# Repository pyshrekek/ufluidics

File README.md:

# ufluidics

Firmware for an Elegoo Mega 2560 R3 driving five NEMA17 syringe pumps on a microfluidic device.

Two input pumps push a fixed total flow into the chip at a fixed ratio to each other.
Three output pumps withdraw exactly that same total, split three ways.
Two potentiometers set the output split live, and a maintained switch arms and disarms the system.

Mass balance holds by construction, not by tuning.
No pump is ever commanded directly: one total flow constant drives both inputs (by a fixed ratio) and all three outputs (by fractions that sum to 1.0).
There is one source of truth for flow in the entire program.

## Dependency

**AccelStepper** by Mike McCauley.
Arduino IDE: `Tools > Manage Libraries`, search "AccelStepper", install.

Used in constant-speed mode only.
`runSpeed()` is polled for all five pumps on every loop pass and no acceleration ramp is configured, because steady volumetric flow is the whole point and a ramp would corrupt the mass balance every time a pot moved.

## Repository layout

```
ufluidics/
  README.md          this file - the Mega firmware: wiring, calibration, verification
  HARDWARE.md        PCB spec for the ESP32-S3 revision

  arduino/ufluidics/ Mega 2560 firmware (Arduino IDE)
    ufluidics.ino
    config.h

  firmware/          ESP32-S3 firmware (PlatformIO) - see firmware/README.md
    platformio.ini
    include/config.h
    src/{flow,motion,main}
    data/            LittleFS web assets

  hardware/          KiCad project
    ufluidics.kicad_{pro,sch,pcb}
```

Two builds coexist deliberately: the Mega rig stays working while the ESP32 board is developed. `src/flow.cpp` in the ESP32 build is the AVR flow math ported without modification - see `firmware/README.md`.

**`arduino/ufluidics/` must keep that directory name.** The Arduino IDE requires a sketch folder named exactly after its `.ino`. The repository root can be named anything.

The three KiCad files must also keep a shared basename - that is a KiCad requirement, not a convention. Rename all three together or none.

## Configuration at a glance

At 1/16 microstepping with a 2 mm lead screw and a 14.5 mm syringe bore:

| Quantity | Value |
|---|---|
| steps/mm | 1600 |
| uL/mm | 165.13 |
| steps/uL | 9.69 |
| uL per step | 0.103 |
| Full 10 mL stroke | 60.6 mm, 96 893 steps |

Input flow is **fixed in firmware**, not pot-controlled:

| Pump | Flow | Share of total | Step rate |
|---|---|---|---|
| IN1 | 70 uL/min | 6.25% | 11.3 steps/s |
| IN2 | 1050 uL/min | 93.75% | 169.6 steps/s |
| **Total** | **1120 uL/min (1.12 mL/min)** | - | - |
| OUT3 at a 100% split (worst case) | 1120 uL/min | - | 180.9 steps/s |

The two pots only set how that fixed total is divided between the three outputs.

Flow is smooth: the 0.103 uL step quantum is delivered 11 to 181 times a second, so pulsatility is not a concern.
Peak rate is 181 steps/s against the 2000 steps/s ceiling - an 11x margin, and the shortest step interval is 5.5 ms.
That is comfortably inside where a polled step generator is accurate, so AccelStepper's loop-latency behaviour is not a practical concern at these rates.

### Barrel capacity is the binding constraint - read this

The mechanics are comfortable at these rates; the syringes are what limit a run.
Every barrel is currently 10 mL, and the 15:1 input ratio means they do not last remotely the same time:

| Pump | Flow | 10 mL barrel lasts |
|---|---|---|
| IN1 | 70 uL/min | 143 min |
| IN2 | 1050 uL/min | **9.5 min** |
| OUT3 at a 100% split | 1120 uL/min | **8.9 min** |

**IN2 is the limiting pump.** A 10 mL barrel gives it under a 10 minute run.

For both inputs to exhaust together, barrel volumes want the same 15:1 proportion as the flows - 10 mL on IN1 against 150 mL on IN2 would both run 143 minutes. A 60 mL syringe on IN2 gives 57 minutes, which is usually the practical sweet spot.
Nothing in firmware can extend this; it is a straight volume-over-rate limit.

The output side needs the same thought.
The three outputs collectively receive the full 1120 uL/min, so whichever fills first ends the run - and OUT3 can be handed up to 100% of it.

**Mixing barrel sizes needs a small firmware change.** `SYRINGE_ID_MM` and `SYRINGE_VOLUME_UL` are global today, one geometry shared by all five pumps, which is also what the end-of-travel check uses.
Making them per-pump arrays in the shape of `STEP_PIN[]` and `DIR_SIGN[]` is roughly a 20 line change across both files.

### Note on resolution

The A4988 microstep table tops out at 1/16 (MS1/MS2/MS3 all high); 1/32 is not reachable on that chip.

The 2 mm lead screw compensates for that.
Dropping from 8 mm to 2 mm pitch quadruples resolution at the same microstepping: each step displaces **0.103 uL** instead of 0.41 uL.
That is finer than a DRV8825 at 1/32 would have given on the old 8 mm screw, so the driver is not the limiting factor.

Set `MICROSTEPS` and `LEADSCREW_PITCH_MM` in `config.h` to match the hardware and every derived value follows automatically.

## Wiring

Pins are freely reassignable in `config.h`; nothing depends on a particular port.

| Signal | Pin | Notes |
|---|---|---|
| STEP 1-5 | D22, D23, D24, D25, D26 | `STEP_PIN[]` |
| DIR 1-5 | D30, D31, D32, D33, D34 | `DIR_PIN[]` |
| ENABLE | D28 | Shared across all five drivers, active LOW |
| RUN switch | D2 | Maintained/latching, closed to GND. Internal pullup |
| Pot A | A0 | Sets OUT1's share |
| Pot B | A1 | Sets OUT2's share |
| Status LED | D13 | Off = idle, solid = running, blinking = fault |

The RUN switch needs no pulldown or external pullup - `INPUT_PULLUP` handles it, and an open switch reads HIGH (idle).

Pots wire as dividers: outer legs to 5 V and GND, wiper to the analog pin.

Pump index order is `IN1, IN2, OUT1, OUT2, OUT3`.
OUT1 and OUT2 are pot-controlled; OUT3 absorbs the remainder, so it is the largest stream at typical settings.

### Power

- **Set each driver's Vref before connecting any motor.** For an A4988 with 0.1 ohm sense resistors, `Vref = Imax * 8 * Rsense`; a 1.5 A NEMA17 wants roughly 1.2 V. Getting this wrong at 24 V destroys drivers and cooks motors.
- 24 V goes to driver VMOT only. The Mega runs from USB or its own barrel jack.
- **Grounds must be common** between the 24 V supply and the Mega.
- Put a 100 uF electrolytic across VMOT/GND at each driver, close to the pins.
- Never hot-plug a stepper into a powered driver. It kills the output stage.
- Confirm the MS jumpers match `MICROSTEPS`. A mismatch scales every flow rate by 2x to 16x with no error indication anywhere.

## Operation

Load **input syringes full** and **output syringes empty** before arming.
The firmware tracks travel by counting steps from this assumed starting state; it has no way to sense actual plunger position.

The RUN control is a **maintained (latching) switch**, so its position is the request - the firmware follows the level rather than toggling on an edge.

- **Close** the switch to arm. The LED goes solid and the drivers energise.
- **Open** it to disarm.
- Turn any pot at any time. Total flow and the split update live without stopping flow.
- If any syringe reaches the end of its stroke, the system halts itself, disables the drivers, blinks the LED, and prints which pump hit the limit. Open the switch to acknowledge - that resets the volume accounting and returns to idle, so it must not happen without an actual syringe reload.

**The system will not arm on power-up from an already-closed switch.** The switch has to be seen open at least once first (`g_armInhibit`). Without that, restoring power to a rig left switched on would start pumping with nobody present and with syringe positions assumed rather than known. The banner prints `[arm] RUN switch open, ready to arm` once the interlock clears.

Serial telemetry runs at **115200 baud**, one line per second:

```
state   OUT1/OUT2/OUT3 split   then per pump: uL/min (syringe uL)
RUN     50.0/30.0/20.0%   IN1 100.0(9987) IN2 1000.0(9871) OUT1 550.0(129) OUT2 330.0(77) OUT3 220.0(51)
```

The column header re-emits every 20 rows (`TELEMETRY_HEADER_ROWS`), so opening the serial monitor after boot still tells you what the numbers are - no reset needed.
Inputs report volume **remaining** in the barrel, outputs report volume **accumulated**.

The boot banner prints `uL per step`, both fixed input flows with their step rates, the input ratio, total flow, and the fastest pump's rate. Those are the numbers that tell you whether the mechanics suit the configured flow.

## Details worth knowing

**Telemetry is non-blocking.**
`Serial.print()` blocks once the 64-byte UART buffer fills, and anything that blocks stops `runSpeed()` from being polled.
AccelStepper timestamps each step as it happens rather than against a fixed schedule (its own source comments "does not account for costs in step()"), so a stalled loop turns directly into lost volume that is never made up.
Status lines are therefore staged in a buffer and drained only as fast as the UART has room.
A slow terminal throttles telemetry instead of corrupting flow.

**Both speed limits are enforced at compile time.**
`AccelStepper::setSpeed()` silently clamps against `setMaxSpeed()`, so a too-fast configuration would quietly under-deliver with no visible symptom.
`static_assert`s in `config.h` check the fastest possible pump (`MAX_PUMP_SPS`, OUT3 at a 100% split) and the slowest (`MIN_IN1_SPS`, always IN1) against the configured flow.
A wide input ratio squeezes both ends of that window at once, which is why the checks are paired: raising `IN2_TO_IN1_RATIO` pushes IN2 toward the ceiling and IN1 toward the floor simultaneously.

**The pot span has margins at both ends, and they are required.**
`POT_DEADBAND` only lets the applied value move once the reading shifts by more than 8 counts.
At the ends of travel there is nothing beyond to push it those last counts, so it strands short of the rail and 0%/100% become unreachable - the symptom is OUT3 bottoming out around 10.6% instead of 10.0% and topping out at 99.5% instead of 100%.
Real pots compound it, since track end resistance often stops the wiper reading a true 0 or 1023.
`POT_RAW_MIN`/`POT_RAW_MAX` discard the outer counts of the sweep so both rails are always reachable, and a `static_assert` enforces that the margin clears the deadband.

**There is a minimum speed, and it is a correctness limit.**
`setSpeed()` computes `_stepInterval = 1000000.0 / speed` into an `unsigned long`.
At 1 uL/min a pot near the bottom of its travel can command about 7.1e-5 steps/s, which works out to an interval of 1.4e10 us against a uint32 ceiling of 4.29e9.
It wraps, and the pump then runs roughly 3x **faster** than commanded rather than slower.
`applySpeeds()` therefore floors anything below `MIN_SPEED_SPS` to a true stop.
Verified against the library source, not assumed.

## Tuning

Everything of interest is in `config.h`:

```c
#define IN1_FLOW_UL_MIN       70.0f   // fixed; IN1 takes 1/16 of total
#define IN2_TO_IN1_RATIO      15.0f   // -> IN2 1050, total 1120 uL/min
#define OUT_POT_MAX_FRAC   0.45f   // per-pot ceiling; OUT3 floor is 1 - 2x this
#define SYRINGE_ID_MM      14.5f   // MEASURE THIS
#define MICROSTEPS         16      // must match the driver jumpers
#define LEADSCREW_PITCH_MM 2.0f    // must match the actual screw
#define POT_RAW_MIN        16      // pot end margins; must exceed POT_DEADBAND
#define POT_RAW_MAX        1007
```

If a pump runs backwards, flip its entry in `DIR_SIGN[]`.
Do not rewire.

## Verification

1. **Compile.** Arduino IDE with the board set to Arduino Mega 2560, or `arduino-cli compile --fqbn arduino:avr:mega .`
2. **Bench test with no motors and no 24 V.** USB power only. Open the serial monitor, confirm the arm interlock reports the switch open, close the switch, sweep both pots. The three output percentages must always sum to 100.0. Both pots at minimum must give OUT3 exactly 100.0%, both at maximum exactly 10.0%. If the endpoints come up short (10.6%, 99.5%), the pot end margins are too small - raise `POT_RAW_MIN` and lower `POT_RAW_MAX`.
3. **Watch the STEP pins** on D22-D26 before any liquid is involved. At 1 uL/min this is not a scope measurement - it is one pulse every 12.4 s on each input pump, so an LED on the pin or a logic analyzer in single-shot is the practical tool. Count the interval against the boot banner. This is the only way to catch a microstepping jumper mismatch or a wrong `LEADSCREW_PITCH_MM`, which are otherwise completely invisible.
4. **Dry motor run** with motors off the lead screws and 24 V on. The two input motors turn one way, the three outputs the other. Expect visibly discrete steps, not rotation - that is the flow rate, not a fault.
4b. **Sanity-check the timing before trusting a long run.** Not needed at these rates - the pumps step 16 to 291 times a second, so behaviour is observable in real time. Debugging a system that steps twice a minute is otherwise very slow going.
5. **Gravimetric calibration.** This is the test that validates the whole chain. Run one input pump alone for a timed 60 s into a tared weigh boat and compare mass in mg against expected uL. A consistent percentage error means `SYRINGE_ID_MM` is wrong; correct it and the error disappears from all five pumps at once, because everything derives from that one constant.
6. **Fault check.** Temporarily set `SYRINGE_VOLUME_UL` to 200, run, and confirm the system halts and blinks on schedule.

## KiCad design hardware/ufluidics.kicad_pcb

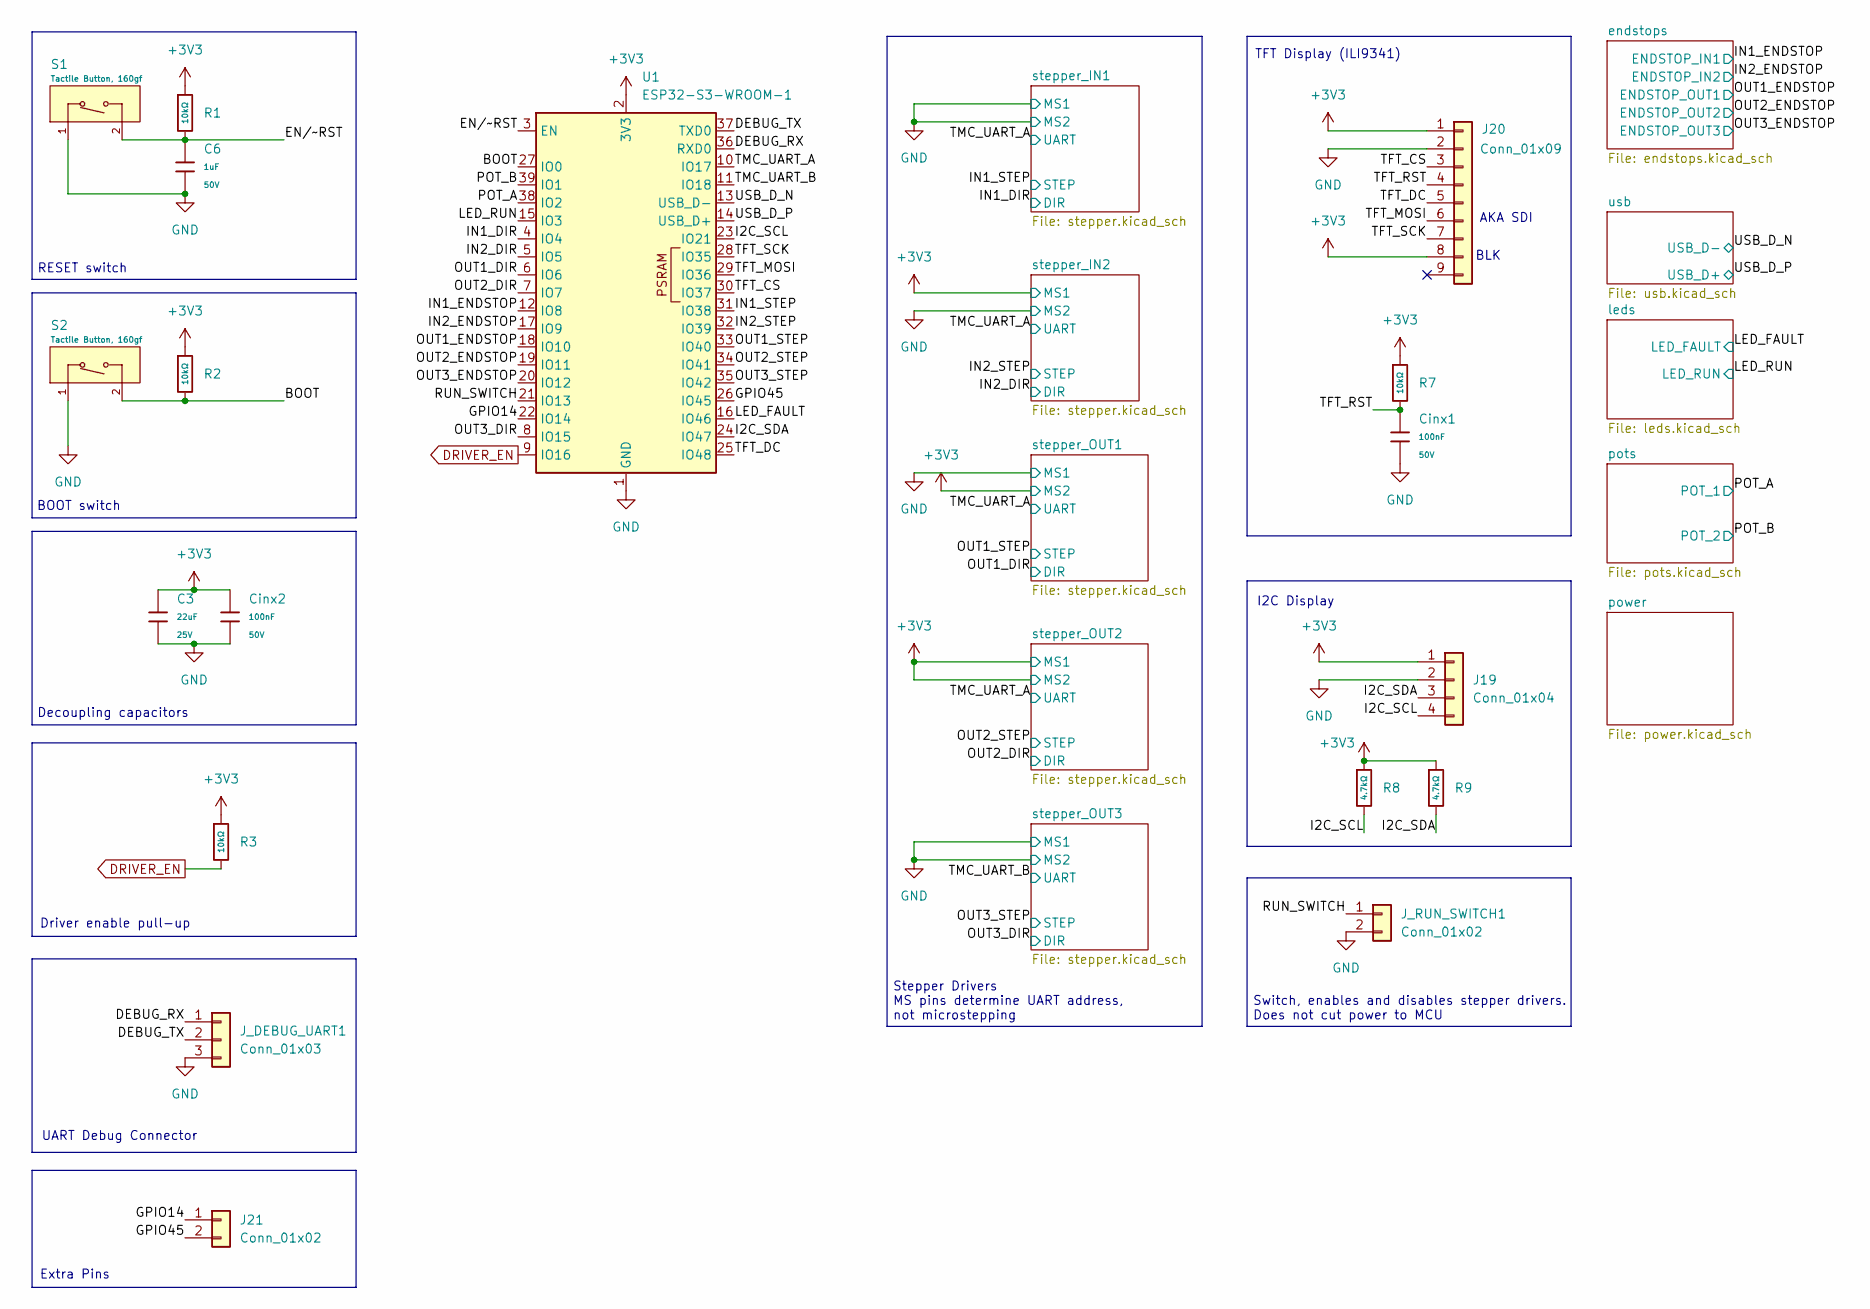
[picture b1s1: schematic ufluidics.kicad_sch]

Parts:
C3: 22uF; C_0805; Voltage Rated 25V; Tolerance ±20%; Part CL21A226MAQNNNE; LCSC C45783
C6: 1uF; C_0805; Voltage Rated 50V; Tolerance ±10%; Part CL21B105KBFNNNE; LCSC C28323
Cinx1, Cinx2: 100nF; C_0402; Voltage Rated 50V; Tolerance ±10%; Part CL05B104KB54PNC; LCSC C307331
J19: Conn_01x04; JST_XH_B4B-XH-A_1x04_P2.50mm_Vertical
J20: Conn_01x09; JST_XH_B9B-XH-A_1x09_P2.50mm_Vertical
J21: Conn_01x02; PinHeader_1x02_P2.54mm_Vertical
J_DEBUG_UART1: Conn_01x03; JST_XH_B3B-XH-A_1x03_P2.50mm_Vertical
J_RUN_SWITCH1: Conn_01x02; JST_XH_B2B-XH-A_1x02_P2.50mm_Vertical
R1, R2, R3, R7: 10kΩ; R_0603; Overload Voltage (Max) 75V; Tolerance ±1%; Part 0603WAF1002T5E; LCSC C25804
R8, R9: 4.7kΩ; R_0603; Overload Voltage (Max) 75V; Tolerance ±1%; Part 0603WAF4701T5E; LCSC C23162
S1, S2: Tactile Button, 160gf; SW_TS-1088-AR02016; Voltage Rating (Dc) 12V; Part TS-1088-AR02016; LCSC C720477
U1: ESP32-S3-WROOM-1

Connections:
+3V3: C3.1, Cinx2.1, J19.1, J20.1, J20.8, R1.1, R2.1, R3.1, R7.1, R8.1, R9.1, U1.2 (3V3); also elsewhere on the board
/BOOT: R2.2, S2.2 (B), U1.27 (IO0)
/DEBUG_RX: J_DEBUG_UART1.1, U1.36 (RXD0)
/DEBUG_TX: J_DEBUG_UART1.2, U1.37 (TXD0)
/EN/~RST: C6.1, R1.2, S1.2 (B), U1.3 (EN)
/GPIO14: J21.1, U1.22 (IO14)
/GPIO45: J21.2, U1.26 (IO45)
/I2C_SCL: J19.4, R8.2, U1.23 (IO21)
/I2C_SDA: J19.3, R9.2, U1.24 (IO47)
/IN1_DIR: U1.4 (IO4); also elsewhere on the board
/IN1_ENDSTOP: U1.12 (IO8); also elsewhere on the board
/IN1_STEP: U1.31 (IO38); also elsewhere on the board
/IN2_DIR: U1.5 (IO5); also elsewhere on the board
/IN2_ENDSTOP: U1.17 (IO9); also elsewhere on the board
/IN2_STEP: U1.32 (IO39); also elsewhere on the board
/LED_FAULT: U1.16 (IO46); also elsewhere on the board
/LED_RUN: U1.15 (IO3); also elsewhere on the board
/OUT1_DIR: U1.6 (IO6); also elsewhere on the board
/OUT1_ENDSTOP: U1.18 (IO10); also elsewhere on the board
/OUT1_STEP: U1.33 (IO40); also elsewhere on the board
/OUT2_DIR: U1.7 (IO7); also elsewhere on the board
/OUT2_ENDSTOP: U1.19 (IO11); also elsewhere on the board
/OUT2_STEP: U1.34 (IO41); also elsewhere on the board
/OUT3_DIR: U1.8 (IO15); also elsewhere on the board
/OUT3_ENDSTOP: U1.20 (IO12); also elsewhere on the board
/OUT3_STEP: U1.35 (IO42); also elsewhere on the board
/POT_A: U1.38 (IO2); also elsewhere on the board
/POT_B: U1.39 (IO1); also elsewhere on the board
/RUN_SWITCH: J_RUN_SWITCH1.1, U1.21 (IO13)
/TFT_CS: J20.3, U1.30 (IO37)
/TFT_DC: J20.5, U1.25 (IO48)
/TFT_MOSI: J20.6, U1.29 (IO36)
/TFT_RST: Cinx1.1, J20.4, R7.2
/TFT_SCK: J20.7, U1.28 (IO35)
/TMC_UART_A: U1.10 (IO17); also elsewhere on the board
/TMC_UART_B: U1.11 (IO18); also elsewhere on the board
/USB_D_N: U1.13 (USB_D-); also elsewhere on the board
/USB_D_P: U1.14 (USB_D+); also elsewhere on the board
DRIVER_EN: R3.2, U1.9 (IO16); also elsewhere on the board
GND: C3.2, C6.2, Cinx1.2, Cinx2.2, J19.2, J20.2, J_DEBUG_UART1.3, J_RUN_SWITCH1.2, S1.1 (A), S2.1 (A), U1.1 (GND), U1.40 (GND), U1.41 (GND); also elsewhere on the board

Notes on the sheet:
AKA SDI
BOOT switch
UART Debug Connector
I2C Display
Driver enable pull-up
Stepper Drivers MS pins determine UART address, not microstepping
BLK
RESET switch
Extra Pins
Switch, enables and disables stepper drivers. Does not cut power to MCU
TFT Display (ILI9341)
Decoupling capacitors

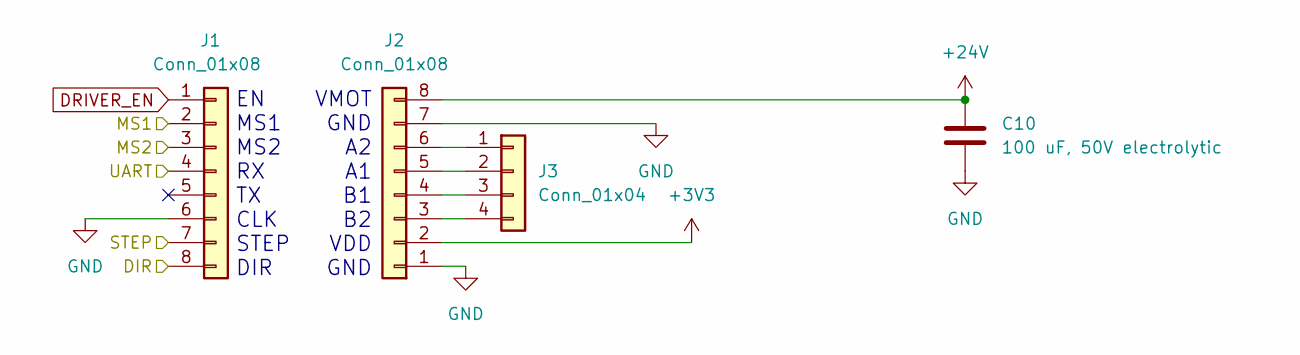
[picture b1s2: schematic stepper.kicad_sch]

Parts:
C10: 100 uF, 50V electrolytic; C_Radial_D8.0mm_H11.5mm_P3.50mm; MFR Part# KM107M050F12RR0VH2FP0; JLC Part# C2749
J1, J2: Conn_01x08; PinSocket_1x08_P2.54mm_Vertical
J3: Conn_01x04; PinHeader_1x04_P2.54mm_Vertical

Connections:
+3V3: J2.2; also elsewhere on the board
+24V: C10.1, J2.8; also elsewhere on the board
/IN1_DIR: J1.8; also elsewhere on the board
/IN1_STEP: J1.7; also elsewhere on the board
/TMC_UART_A: J1.4; also elsewhere on the board
DRIVER_EN: J1.1; also elsewhere on the board
GND: C10.2, J1.2, J1.3, J1.6, J2.1, J2.7; also elsewhere on the board
unnamed: J2.3, J3.4
unnamed: J2.4, J3.3
unnamed: J2.5, J3.2
unnamed: J2.6, J3.1

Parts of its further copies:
C11, C12, C13, C14: 100 uF, 50V electrolytic; C_Radial_D8.0mm_H11.5mm_P3.50mm; MFR Part# KM107M050F12RR0VH2FP0; JLC Part# C2749
J4, J5, J7, J8, J10, J11, J13, J14: Conn_01x08; PinSocket_1x08_P2.54mm_Vertical
J6, J9, J12, J15: Conn_01x04; PinHeader_1x04_P2.54mm_Vertical

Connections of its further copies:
+3V3: J4.2, J5.2, J7.3, J8.2, J10.2, J10.3, J11.2, J14.2; also elsewhere on the board
+24V: C11.1, C12.1, C13.1, C14.1, J5.8, J8.8, J11.8, J14.8; also elsewhere on the board
/IN2_DIR: J4.8; also elsewhere on the board
/IN2_STEP: J4.7; also elsewhere on the board
/OUT1_DIR: J7.8; also elsewhere on the board
/OUT1_STEP: J7.7; also elsewhere on the board
/OUT2_DIR: J10.8; also elsewhere on the board
/OUT2_STEP: J10.7; also elsewhere on the board
/OUT3_DIR: J13.8; also elsewhere on the board
/OUT3_STEP: J13.7; also elsewhere on the board
/TMC_UART_A: J4.4, J7.4, J10.4; also elsewhere on the board
/TMC_UART_B: J13.4; also elsewhere on the board
DRIVER_EN: J4.1, J7.1, J10.1, J13.1; also elsewhere on the board
GND: C11.2, C12.2, C13.2, C14.2, J4.3, J4.6, J5.1, J5.7, J7.2, J7.6, J8.1, J8.7, J10.6, J11.1, J11.7, J13.2, J13.3, J13.6, J14.1, J14.7; also elsewhere on the board
unnamed: J5.3, J6.4
unnamed: J5.4, J6.3
unnamed: J5.5, J6.2
unnamed: J5.6, J6.1
unnamed: J8.3, J9.4
unnamed: J8.4, J9.3
unnamed: J8.5, J9.2
unnamed: J8.6, J9.1
unnamed: J11.3, J12.4
unnamed: J11.4, J12.3
unnamed: J11.5, J12.2
unnamed: J11.6, J12.1
unnamed: J14.3, J15.4
unnamed: J14.4, J15.3
unnamed: J14.5, J15.2
unnamed: J14.6, J15.1

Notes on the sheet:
VMOT GND A2 A1 B1 B2 VDD GND
EN MS1 MS2 RX TX CLK STEP DIR

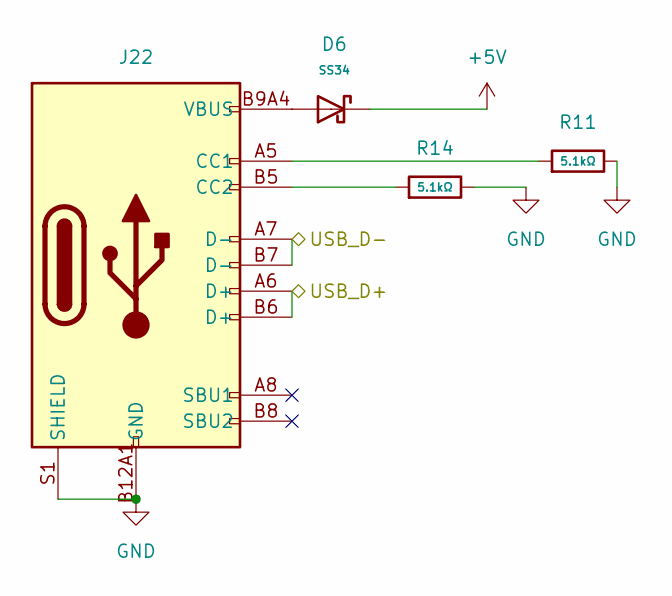
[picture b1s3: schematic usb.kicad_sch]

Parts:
D6: SS34; D_SMA; Forward Voltage (Vf@If) 550mV@3A; Reverse Voltage (Vr) 40V; Part SS34; LCSC C8678
J22: Connector, USB-TYPE-C-16P; TYPE-C-SMD_HX-TYPE-C-16PIN; LCSC C2927039
R11, R14: 5.1kΩ; R_0603; Overload Voltage (Max) 75V; Tolerance ±1%; Part 0603WAF5101T5E; LCSC C23186

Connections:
+5V: D6.1; also elsewhere on the board
/USB_D_N: J22.A7 (D-), J22.B7 (D-); also elsewhere on the board
/USB_D_P: J22.A6 (D+), J22.B6 (D+); also elsewhere on the board
GND: J22.A12B1 (GND), J22.B12A1 (GND), J22.S1 (SHIELD), R11.2, R14.2; also elsewhere on the board
unnamed: D6.2, J22.A9B4 (VBUS), J22.B9A4 (VBUS)
unnamed: J22.A5 (CC1), R11.1
unnamed: J22.B5 (CC2), R14.1

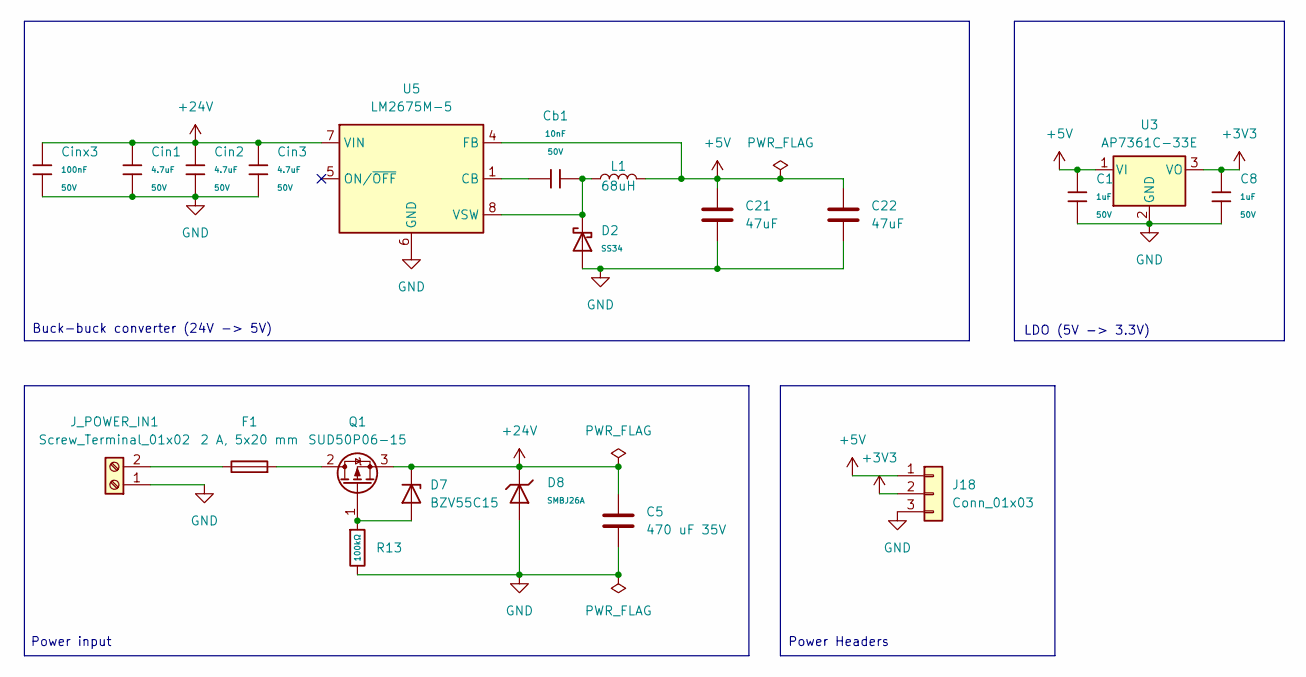
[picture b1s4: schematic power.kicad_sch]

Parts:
C1, C8: 1uF; C_0805; Voltage Rated 50V; Tolerance ±10%; Part CL21B105KBFNNNE; LCSC C28323
C5: 470 uF 35V; C_Radial_D10.0mm_H16.0mm_P5.00mm; MFR Part# ERS1VM471G16OT; JLC Part# C106703
C21, C22: 47uF; C_1210_3225Metric; MFR Part# GRM32ER61C476KE15L; JLC Part# C77101
Cb1: 10nF; C_0805; Voltage Rated 50V; Tolerance ±10%; Part CL21B103KBANNNC; LCSC C1710
Cin1, Cin2, Cin3: 4.7uF; C_1206; Voltage Rated 50V; Tolerance ±10%; Part 1206B475K500NT; LCSC C29823
Cinx3: 100nF; C_0402; Voltage Rated 50V; Tolerance ±10%; Part CL05B104KB54PNC; LCSC C307331
D2: SS34; D_SMA; Forward Voltage (Vf@If) 550mV@3A; Reverse Voltage (Vr) 40V; Part SS34; LCSC C8678
D7: BZV55C15; D_MiniMELF
D8: SMBJ26A; D_SMB; Part SMBJ26A; LCSC C19077580
F1: 2 A, 5x20 mm; Fuseholder_Cylinder-5x20mm_Stelvio-Kontek_PTF78_Horizontal_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; JLC Part# C3130
J18: Conn_01x03; PinHeader_1x03_P2.54mm_Vertical
J_POWER_IN1: Screw_Terminal_01x02; TerminalBlock_4Ucon_1x02_P3.50mm_Horizontal
L1: 68uH; L_SXN_SMDRI127; MFR Part# SMDRI127-680MT; JLC Part# C9907
Q1: SUD50P06-15; TO-252-2
R13: 100kΩ; R_0603; Overload Voltage (Max) 75V; Tolerance ±1%; Part 0603WAF1003T5E; LCSC C25803
U3: AP7361C-33E; SOT-223-3_TabPin2
U5: LM2675M-5; SOIC-8_3.9x4.9mm_P1.27mm

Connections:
+3V3: C8.1, J18.2, U3.3 (VO); also elsewhere on the board
+5V: C1.1, C21.1, C22.1, J18.1, L1.2, U3.1 (VI), U5.4 (FB); also elsewhere on the board
+24V: C5.1, Cin1.1, Cin2.1, Cin3.1, Cinx3.1, D7.1 (K), D8.1, Q1.3 (S), U5.7 (VIN); also elsewhere on the board
GND: C1.2, C5.2, C8.2, C21.2, C22.2, Cin1.2, Cin2.2, Cin3.2, Cinx3.2, D2.2, D8.2, J18.3, J_POWER_IN1.1, R13.2, U3.2 (GND), U5.6 (GND); also elsewhere on the board
unnamed: D7.2 (A), Q1.1 (G), R13.1
unnamed: F1.1, J_POWER_IN1.2
unnamed: F1.2, Q1.2 (D)
unnamed: Cb1.1, U5.1 (CB)
unnamed: Cb1.2, D2.1, L1.1, U5.8 (VSW)

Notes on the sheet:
Power input
Power Headers
LDO (5V -> 3.3V)
Buck-buck converter (24V -> 5V)

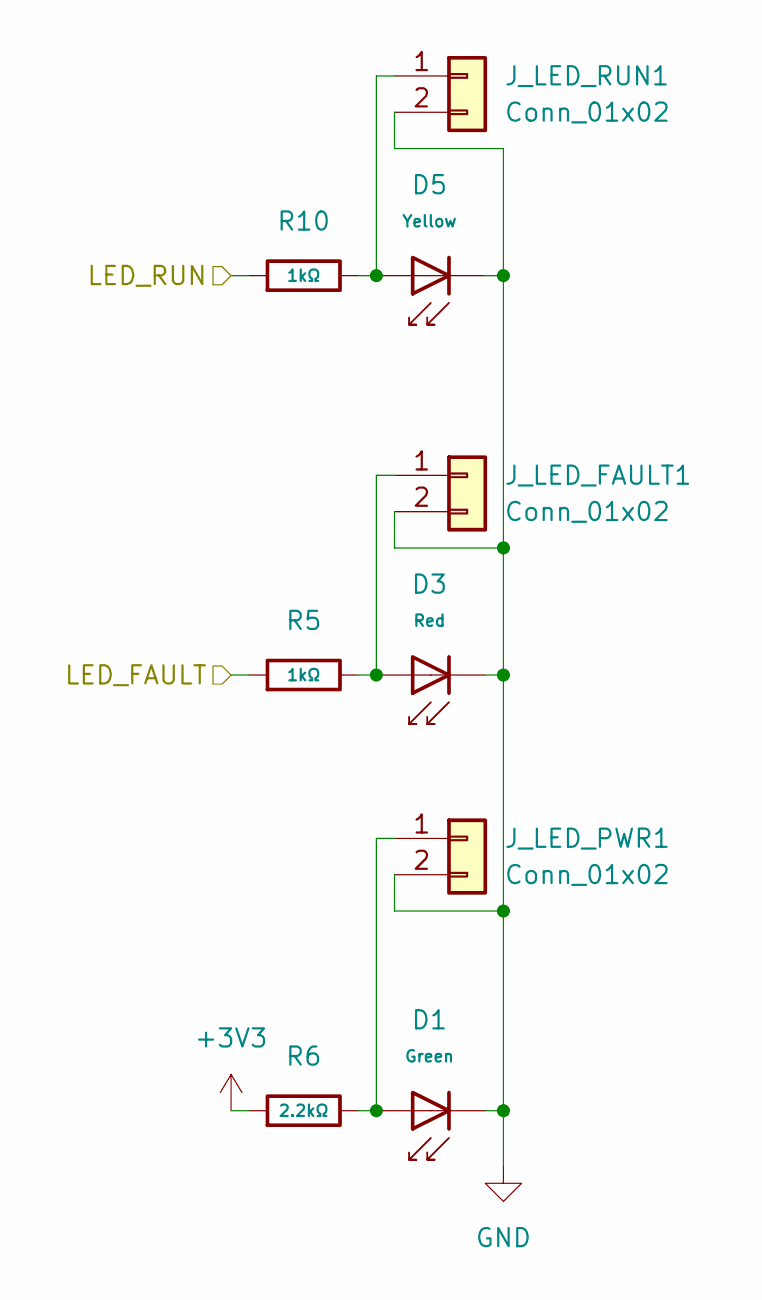
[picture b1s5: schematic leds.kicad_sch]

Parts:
D1: Green; D_0805; Part KT-0805G; LCSC C2297
D3: Red; D_0603; Part KT-0603R; LCSC C2286
D5: Yellow; D_0603; Forward Voltage (VF) 1.6V~2.6V; Part NCD0603Y2; LCSC C89811
J_LED_FAULT1: Conn_01x02; JST_PH_B2B-PH-K_1x02_P2.00mm_Vertical
J_LED_PWR1: Conn_01x02; JST_PH_B2B-PH-K_1x02_P2.00mm_Vertical
J_LED_RUN1: Conn_01x02; JST_PH_B2B-PH-K_1x02_P2.00mm_Vertical
R5, R10: 1kΩ; R_0603; Overload Voltage (Max) 75V; Tolerance ±1%; Part 0603WAF1001T5E; LCSC C21190
R6: 2.2kΩ; R_0603; Overload Voltage (Max) 75V; Tolerance ±1%; Part 0603WAF2201T5E; LCSC C4190

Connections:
+3V3: R6.1; also elsewhere on the board
/LED_FAULT: R5.1; also elsewhere on the board
/LED_RUN: R10.1; also elsewhere on the board
GND: D1.1, D3.1, D5.1, J_LED_FAULT1.2, J_LED_PWR1.2, J_LED_RUN1.2; also elsewhere on the board
unnamed: D3.2, J_LED_FAULT1.1, R5.2
unnamed: D1.2, J_LED_PWR1.1, R6.2
unnamed: D5.2, J_LED_RUN1.1, R10.2

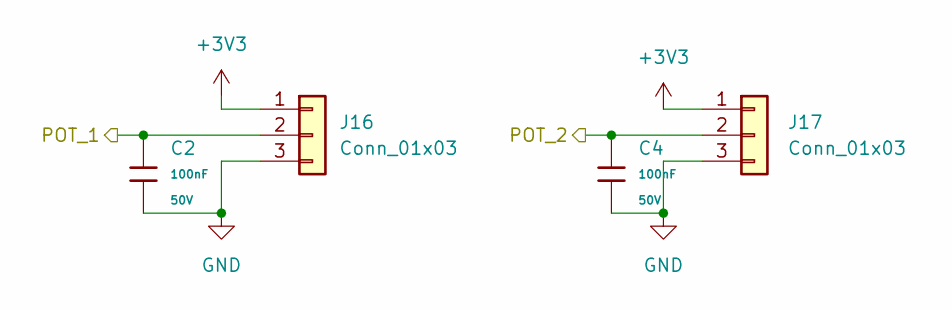
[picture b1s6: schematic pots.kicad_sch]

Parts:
C2, C4: 100nF; C_0402; Voltage Rated 50V; Tolerance ±10%; Part CL05B104KB54PNC; LCSC C307331
J16, J17: Conn_01x03; JST_XH_B3B-XH-A_1x03_P2.50mm_Vertical

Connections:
+3V3: J16.1, J17.1; also elsewhere on the board
/POT_A: C2.1, J16.2; also elsewhere on the board
/POT_B: C4.1, J17.2; also elsewhere on the board
GND: C2.2, C4.2, J16.3, J17.3; also elsewhere on the board

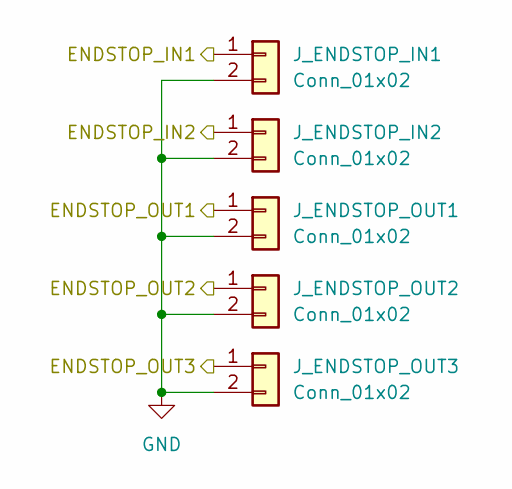
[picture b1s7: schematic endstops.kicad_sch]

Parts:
J_ENDSTOP_IN1, J_ENDSTOP_IN2: Conn_01x02; JST_XH_B2B-XH-A_1x02_P2.50mm_Vertical
J_ENDSTOP_OUT1, J_ENDSTOP_OUT2, J_ENDSTOP_OUT3: Conn_01x02; JST_XH_B2B-XH-A_1x02_P2.50mm_Vertical

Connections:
/IN1_ENDSTOP: J_ENDSTOP_IN1.1; also elsewhere on the board
/IN2_ENDSTOP: J_ENDSTOP_IN2.1; also elsewhere on the board
/OUT1_ENDSTOP: J_ENDSTOP_OUT1.1; also elsewhere on the board
/OUT2_ENDSTOP: J_ENDSTOP_OUT2.1; also elsewhere on the board
/OUT3_ENDSTOP: J_ENDSTOP_OUT3.1; also elsewhere on the board
GND: J_ENDSTOP_IN1.2, J_ENDSTOP_IN2.2, J_ENDSTOP_OUT1.2, J_ENDSTOP_OUT2.2, J_ENDSTOP_OUT3.2; also elsewhere on the board

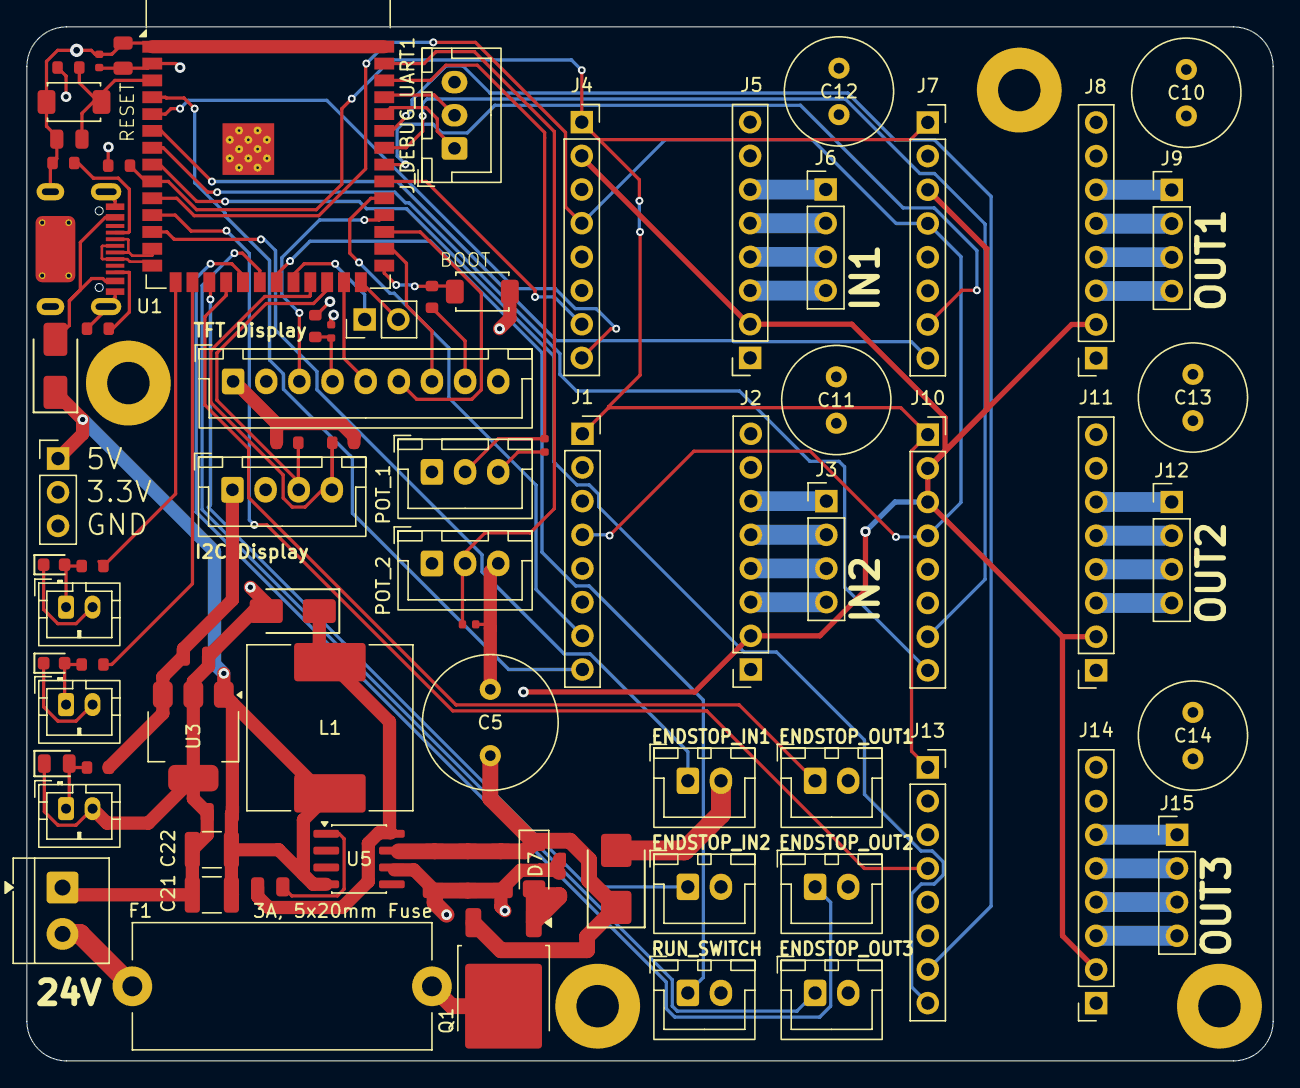
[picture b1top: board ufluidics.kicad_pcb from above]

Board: 4 copper layers, 94.0 x 78.0 mm, 81 parts (0 on the bottom side), 73 nets.

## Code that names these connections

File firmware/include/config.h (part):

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#define STEP_GPIO_MASK  0x7C0u         // bits 6..10 of OUT1 = GPIO38..42

#define EN_PIN          16             // shared across all 5 drivers, active LOW
#define TMC_UART_A_PIN  17             // single-wire UART, drivers 0-3
#define TMC_UART_B_PIN  18             // single-wire UART, driver 4

#define POT_A_PIN       1              // ADC1_CH0 - OUT1 fraction
#define POT_B_PIN       2              // ADC1_CH1 - OUT2 fraction

#define RUN_SWITCH_PIN  13             // maintained, closed to GND
#define ESTOP_SENSE_PIN 14             // sense only; the cut is hardware
// LEDs sit on strapping pins, which is safe here and deliberate.
//
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// deselected in favor of external JTAG pins this board does not expose -
// inconvenient, not boot-breaking.
//
// GPIO45 (VDD_SPI strap) is free again after this move - nothing populates
// it, so it costs nothing to leave unused.
//
// The alternative, GPIO43/44, is UART0. Those pins stay free so there is a
// serial recovery port if native USB is ever unusable, and so the ROM boot log
// does not flicker an indicator LED on every reset.
#define LED_RUN_PIN     3              // JTAG source strap, verify at bring-up
#define LED_FAULT_PIN   46             // ROM-print strap, pulled low at reset

#define I2C_SDA_PIN     47
#define I2C_SCL_PIN     21

// SPI display header, N16 ONLY.
//
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// IO35. Anything in 22-34 is either absent or bonded to the internal flash.
#ifndef BOARD_HAS_PSRAM
  #define TFT_SPI_AVAILABLE 1
  #define TFT_SCK_PIN     35
  #define TFT_MOSI_PIN    36
  #define TFT_CS_PIN      37
  #define TFT_DC_PIN      48   // free; DevKitC-1 wires it to an RGB LED
                               // RST -> board reset net, no GPIO
#else
  #define TFT_SPI_AVAILABLE 0
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static const uint8_t STEP_PIN[N_PUMPS]  = { 38, 39, 40, 41, 42 };
static const uint8_t DIR_PIN[N_PUMPS]   = { 4, 5, 6, 7, 15 };
static const uint8_t ENDSTOP_PIN[N_PUMPS] = { 8, 9, 10, 11, 12 };
static const uint8_t POT_PIN[N_POTS]    = { POT_A_PIN, POT_B_PIN };

// Direction each pump runs in. Inputs dispense, outputs withdraw.
// If a pump physically runs the wrong way, flip its entry here. Do not rewire.
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// which is invisible until the board is built.
#define PIN_EXISTS(p)  (((p) <= 21) || ((p) >= 35 && (p) <= 48))

static_assert(PIN_EXISTS(EN_PIN)          && PIN_EXISTS(TMC_UART_A_PIN)  &&
              PIN_EXISTS(TMC_UART_B_PIN)  && PIN_EXISTS(POT_A_PIN)       &&
              PIN_EXISTS(POT_B_PIN)       && PIN_EXISTS(RUN_SWITCH_PIN)  &&
              PIN_EXISTS(ESTOP_SENSE_PIN) && PIN_EXISTS(LED_RUN_PIN)     &&
              PIN_EXISTS(LED_FAULT_PIN)   && PIN_EXISTS(I2C_SDA_PIN)     &&
              PIN_EXISTS(I2C_SCL_PIN),
              "pin is not exposed on the ESP32-S3-WROOM-1 module");
static_assert(PIN_EXISTS(STEP_GPIO_BASE) &&
              PIN_EXISTS(STEP_GPIO_BASE + N_PUMPS - 1),
              "STEP range is not exposed on the ESP32-S3-WROOM-1 module");
#if TFT_SPI_AVAILABLE
static_assert(PIN_EXISTS(TFT_SCK_PIN) && PIN_EXISTS(TFT_MOSI_PIN) &&
              PIN_EXISTS(TFT_CS_PIN)  && PIN_EXISTS(TFT_DC_PIN),
              "SPI display pin is not exposed on the module");
#endif

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#ifdef BOARD_HAS_PSRAM
  #define PIN_CLEARS_PSRAM(p) ((p) < 35 || (p) > 37)
  static_assert(PIN_CLEARS_PSRAM(EN_PIN)          &&
                PIN_CLEARS_PSRAM(TMC_UART_A_PIN)  &&
                PIN_CLEARS_PSRAM(TMC_UART_B_PIN)  &&
                PIN_CLEARS_PSRAM(RUN_SWITCH_PIN)  &&
                PIN_CLEARS_PSRAM(ESTOP_SENSE_PIN) &&
                PIN_CLEARS_PSRAM(LED_RUN_PIN)     &&
                PIN_CLEARS_PSRAM(LED_FAULT_PIN)   &&
                PIN_CLEARS_PSRAM(I2C_SDA_PIN)     &&
                PIN_CLEARS_PSRAM(I2C_SCL_PIN),
                "pin collides with octal PSRAM (GPIO35-37) on an R8 module");
  static_assert(PIN_CLEARS_PSRAM(STEP_GPIO_BASE) &&
                PIN_CLEARS_PSRAM(STEP_GPIO_BASE + N_PUMPS - 1),
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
